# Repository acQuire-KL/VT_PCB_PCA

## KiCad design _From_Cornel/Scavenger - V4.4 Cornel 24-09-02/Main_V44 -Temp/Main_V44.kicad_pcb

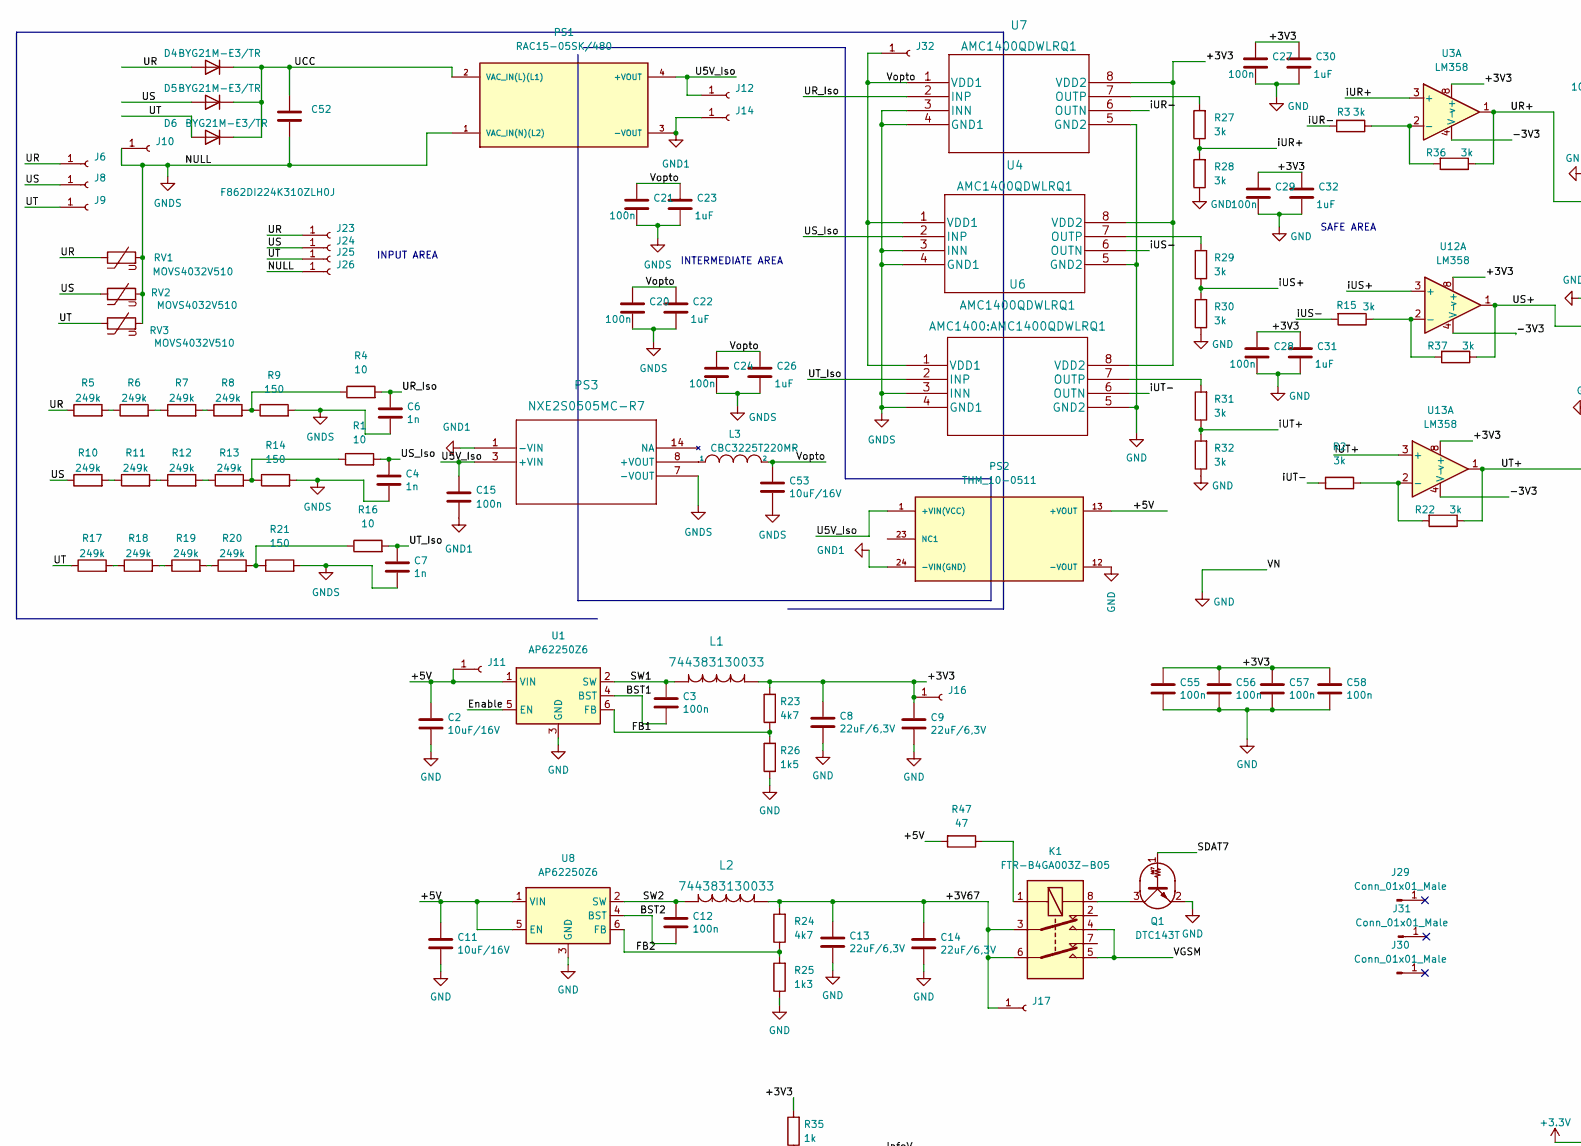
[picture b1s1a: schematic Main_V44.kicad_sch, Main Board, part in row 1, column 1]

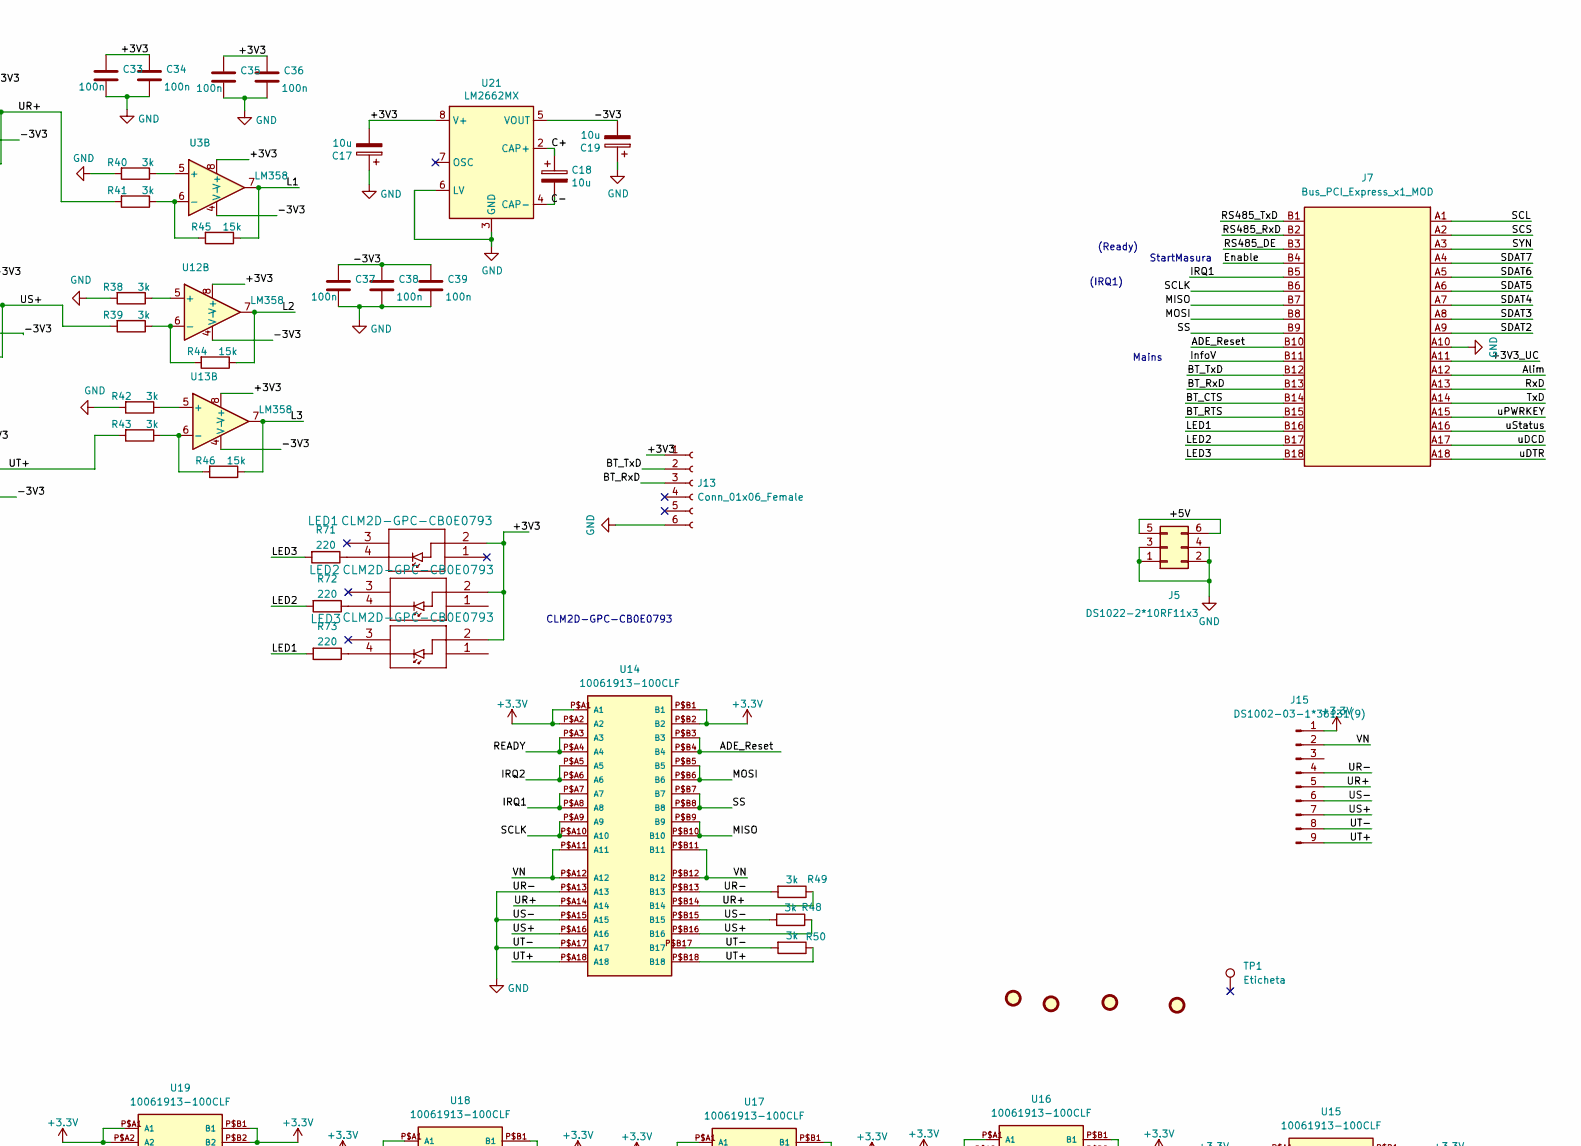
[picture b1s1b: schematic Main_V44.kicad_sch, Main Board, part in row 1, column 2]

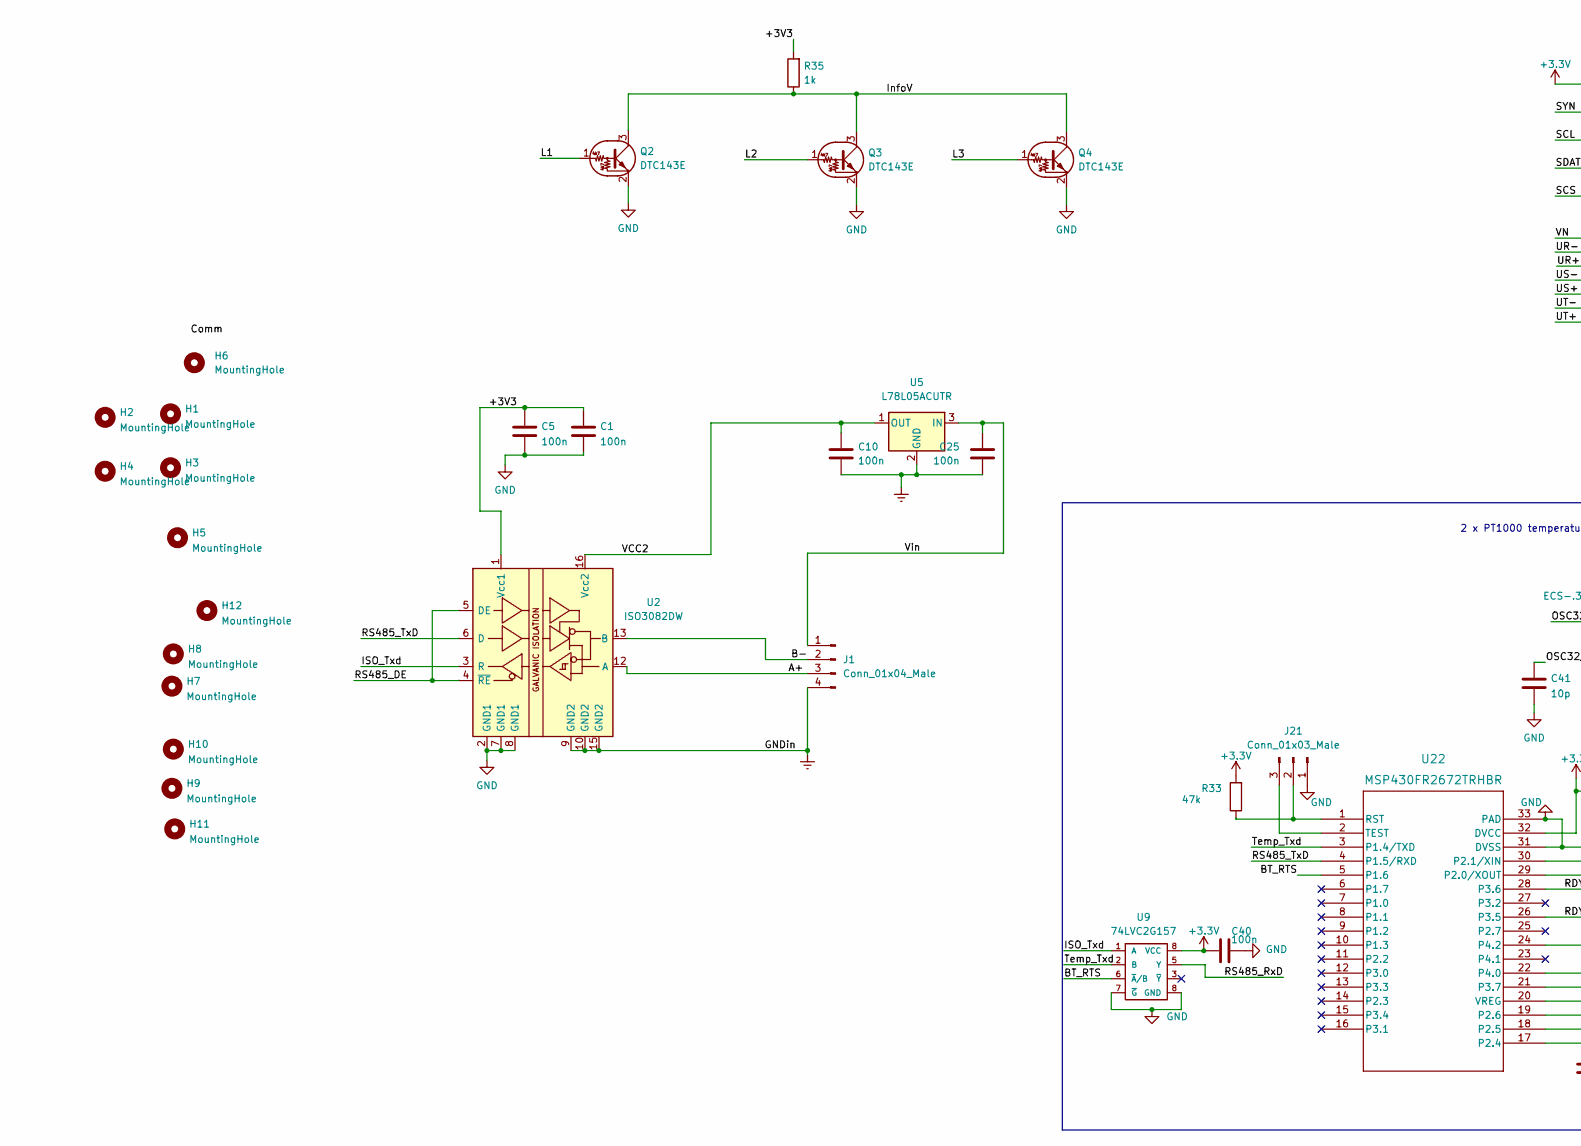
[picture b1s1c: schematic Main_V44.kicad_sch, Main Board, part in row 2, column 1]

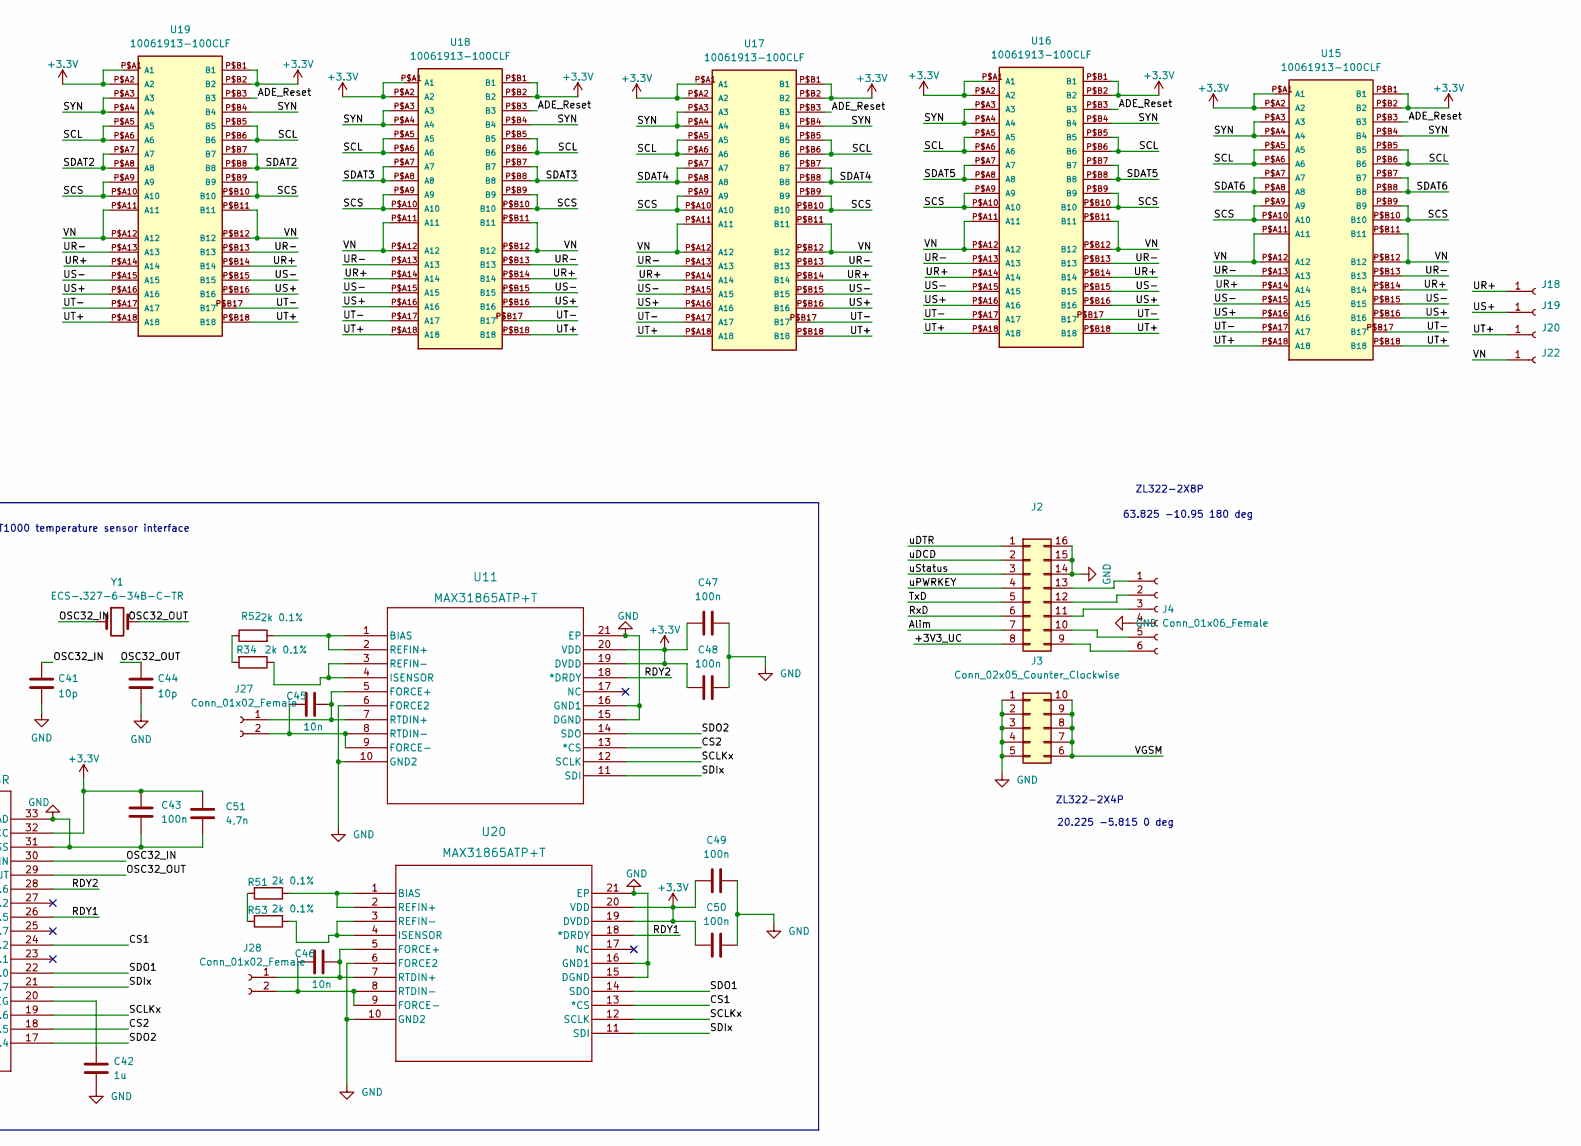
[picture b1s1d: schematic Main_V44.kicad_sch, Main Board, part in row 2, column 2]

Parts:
C1, C3, C5, C10, C12, C15, C20, C21, C24, C25, C27, C28, C29, C33, C34, C35, C36, C37, C38, C39, C40, C43, C47, C48, C49, C50, C55, C56, C57, C58: 100n; C_0603_1608Metric
C2, C11, C53: 10uF/16V; C_1206_3216Metric
C4, C6, C7: 1n; C_0603_1608Metric
C8, C9, C13, C14: 22uF/6,3V; C_1206_3216Metric
C17, C18, C19: 10u; C_1206_3216Metric
C22, C23, C26, C30, C31, C32: 1uF; C_0603_1608Metric
C41, C44: 10p; C_0603_1608Metric
C42: 1u; C_0603_1608Metric
C45, C46: 10n; C_0603_1608Metric
C51: 4,7n; C_0603_1608Metric
C52: F862DI224K310ZLH0J; C_Rect_L24.0mm_W7.0mm_P22.50mm_MKT
D4, D5, D6: BYG21M-E3/TR; D_SMA
FID1, FID2, FID3, FID4: Fiducial; Fiducial_1mm_Mask2mm
H1, H6: MountingHole; MountingHole_3.2mm_M3_ISO14580_Pad_TopBottom
H2, H3, H4, H5, H7, H8, H9, H10, H11, H12: MountingHole; MountingHole_3.2mm_M3
J1: Conn_01x04_Male; A2501-SR04-XH4AWB
J2: Conn_02x08_Counter_Clockwise; PinSocket_2x08_P2.54mm_Vertical_SMD_MOD
J3: Conn_02x05_Counter_Clockwise; PinSocket_2x05_P2.54mm_Vertical_SMD
J4, J13: Conn_01x06_Female; PinSocket_1x06_P2.54mm_Vertical
J5: DS1022-2*10RF11x3; PinHeader_2x03_P2.54mm_Horizontal
J6, J8, J9, J10, J11, J12, J14, J16, J17, J18, J19, J20, J22, J32: Conn_01x01_Female; TestPoint_DELTA
J7: Bus_PCI_Express_x1_MOD; BUS_PCIexpress_x1
J15: DS1002-03-1*36131(9); PinSocket_1x09_P2.54mm_Vertical
J21: Conn_01x03_Male; PinHeader_1x03_P2.54mm_Vertical
J23: Conn_01x01_Female; DELTA_SolderWire-1.5sqmm_1x01_D1.7mm_OD3.9mm
J24, J25, J26: Conn_01x01_Female; DELTA_R_SolderWire-1.5sqmm_1x01_D1.7mm_OD3.9mm
J27, J28: Conn_01x02_Female; TerminalBlock_bornier-2_P5.08mm
J29, J30, J31: Conn_01x01_Male; TestPoint_Pad_5.1x5.1mm
K1: FTR-B4GA003Z-B05; Relay_Fujitsu_FTR-B4GA003
L1, L2: 744383130033
L3: CBC3225T220MR; L_1206_3216Metric
LED1, LED2, LED3: CLM2D-GPC-CB0E0793
PS1: RAC15-05SK/480; CONV_RAC15-12SK_480; PARTREV 0/2022
PS2: THM_10-0511; CONV_THM_10-0511; PARTREV Jan 06, 2021
PS3: NXE2S0505MC-R7; NXE2_SINGLE_SURFACE_MUR
Q1: DTC143T; SOT-23
Q2, Q3, Q4: DTC143E; SOT-23
R1, R4, R16: 10; R_0603_1608Metric
R2, R3, R15, R22, R27, R28, R29, R30, R31, R32, R36, R37, R38, R39, R40, R41, R42, R43, R48, R49, R50: 3k; R_0603_1608Metric
R5, R6, R7, R8, R10, R11, R12, R13, R17, R18, R19, R20: 249k; R_2512_6332Metric
R9, R14, R21: 150; R_0603_1608Metric
R23, R24: 4k7; R_0603_1608Metric
R25: 1k3; R_0603_1608Metric
R26: 1k5; R_0603_1608Metric
R33: 47k; R_0603_1608Metric
R34, R51, R52, R53: 2k 0.1%; R_0603_1608Metric
R35: 1k; R_0603_1608Metric
R44, R45, R46: 15k; R_0603_1608Metric
R47: 47; R_0603_1608Metric
R71, R72, R73: 220; R_0603_1608Metric
RV1, RV2, RV3: MOVS4032V510; MOVS4032V460
TP1: Eticheta
U1, U8: AP62250Z6; SOT-563
U2: ISO3082DW; SOIC-16W_7.5x10.3mm_P1.27mm
U3, U12, U13: LM358; SO-8_3.9x4.9mm_P1.27mm
U4, U6, U7: AMC1400QDWLRQ1
U5: L78L05ACUTR; SOT-89-3
U9: 74LVC2G157; VSSOP-8_2.4x2.1mm_P0.5mm
U11, U20: MAX31865ATP+T; 21-0140L_T2055-5_MXM
U14, U15, U16, U17, U18, U19: 10061913-100CLF; MPN 10061913-100CLF
U21: LM2662MX; SO-8_3.9x4.9mm_P1.27mm
U22: MSP430FR2672TRHBR; VQFN32_5X5_TEX
Y1: ECS-.327-6-34B-C-TR; Crystal_SMD_EuroQuartz_EQ161-2Pin_3.2x1.5mm

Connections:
/+3V3_UC: J2.8, J7.A11
/+3V67: C13.1, C14.1, J17.1, K1.3, K1.6, L2.1, R24.2
/+5V: C2.1, C11.1, J5.5, J5.6, J11.1, PS2.13 (+VOUT), R47.2, U1.1 (VIN), U8.1 (VIN), U8.5 (EN)
/-3V3: C19.2, C37.1, C38.1, C39.1, U3.4 (V-), U12.4 (V-), U13.4 (V-), U21.5 (VOUT)
/A+: J1.3, U2.12 (A)
/ADE_Reset: J7.B10, U14.P$B3 (B3), U14.P$B4 (B4), U15.P$B3 (B3), U16.P$B3 (B3), U17.P$B3 (B3), U18.P$B3 (B3), U19.P$B3 (B3)
/Alim: J2.7, J7.A12
/B-: J1.2, U2.13 (B)
/BST1: C3.2, U1.4 (BST)
/BST2: C12.2, U8.4 (BST)
/BT_CTS: J7.B14
/BT_RTS: J7.B15, U9.6 (~A/B), U22.5 (P1.6)
/BT_RxD: J7.B13, J13.3
/BT_TxD: J7.B12, J13.2
/C+: C18.1, U21.2 (CAP+)
/C-: C18.2, U21.4 (CAP-)
/CS1: U20.13 (*CS), U22.24 (P4.2)
/CS2: U11.13 (*CS), U22.18 (P2.5)
/Enable: J7.B4, U1.5 (EN)
/FB1: R23.1, R26.2, U1.6 (FB)
/FB2: R24.1, R25.2, U8.6 (FB)
/IRQ1: J7.B5, U14.P$A7 (A7), U14.P$A8 (A8)
/IRQ2: U14.P$A5 (A5), U14.P$A6 (A6)
/ISO_Txd: U2.3 (R), U9.1 (A)
/InfoV: J7.B11, Q2.3 (C), Q3.3 (C), Q4.3 (C), R35.1
/L1: Q2.1 (B), R45.1, U3.7
/L2: Q3.1 (B), R44.1, U12.7
/L3: Q4.1 (B), R46.1, U13.7
/LED1: J7.B16, R73.2
/LED2: J7.B17, R72.2
/LED3: J7.B18, R71.2
/MISO: J7.B7, U14.P$B9 (B9), U14.P$B10 (B10)
/MOSI: J7.B8, U14.P$B5 (B5), U14.P$B6 (B6)
/OSC32_IN: C41.1, U22.30 (P2.1/XIN), Y1.1
/OSC32_OUT: C44.1, U22.29 (P2.0/XOUT), Y1.2
/RDY1: U20.18 (*DRDY), U22.26 (P3.5)
/RDY2: U11.18 (*DRDY), U22.28 (P3.6)
/READY: U14.P$A3 (A3), U14.P$A4 (A4)
/RS485_DE: J7.B3, U2.4 (~RE), U2.5 (DE)
/RS485_RxD: J7.B2, U9.5 (Y)
/RS485_TxD: J7.B1, U2.6 (D), U22.4 (P1.5/RXD)
/RxD: J2.6, J7.A13
/SCL: J7.A1, U15.P$A5 (A5), U15.P$A6 (A6), U15.P$B5 (B5), U15.P$B6 (B6), U16.P$A5 (A5), U16.P$A6 (A6), U16.P$B5 (B5), U16.P$B6 (B6), U17.P$A5 (A5), U17.P$A6 (A6), U17.P$B5 (B5), U17.P$B6 (B6), U18.P$A5 (A5), U18.P$A6 (A6), U18.P$B5 (B5), U18.P$B6 (B6), U19.P$A5 (A5), U19.P$A6 (A6), U19.P$B5 (B5), U19.P$B6 (B6)
/SCLK: J7.B6, U14.P$A9 (A9), U14.P$A10 (A10)
/SCLKx: U11.12 (SCLK), U20.12 (SCLK), U22.19 (P2.6)
/SCS: J7.A2, U15.P$A9 (A9), U15.P$A10 (A10), U15.P$B9 (B9), U15.P$B10 (B10), U16.P$A9 (A9), U16.P$A10 (A10), U16.P$B9 (B9), U16.P$B10 (B10), U17.P$A9 (A9), U17.P$A10 (A10), U17.P$B9 (B9), U17.P$B10 (B10), U18.P$A9 (A9), U18.P$A10 (A10), U18.P$B9 (B9), U18.P$B10 (B10), U19.P$A9 (A9), U19.P$A10 (A10), U19.P$B9 (B9), U19.P$B10 (B10)
/SDAT2: J7.A9, U19.P$A7 (A7), U19.P$A8 (A8), U19.P$B7 (B7), U19.P$B8 (B8)
/SDAT3: J7.A8, U18.P$A7 (A7), U18.P$A8 (A8), U18.P$B7 (B7), U18.P$B8 (B8)
/SDAT4: J7.A7, U17.P$A7 (A7), U17.P$A8 (A8), U17.P$B7 (B7), U17.P$B8 (B8)
/SDAT5: J7.A6, U16.P$A7 (A7), U16.P$A8 (A8), U16.P$B7 (B7), U16.P$B8 (B8)
/SDAT6: J7.A5, U15.P$A7 (A7), U15.P$A8 (A8), U15.P$B7 (B7), U15.P$B8 (B8)
/SDAT7: J7.A4, Q1.1 (B)
/SDIx: U11.11 (SDI), U20.11 (SDI), U22.21 (P3.7)
/SDO1: U20.14 (SDO), U22.22 (P4.0)
/SDO2: U11.14 (SDO), U22.17 (P2.4)
/SS: J7.B9, U14.P$B7 (B7), U14.P$B8 (B8)
/SW1: C3.1, L1.2, U1.2 (SW)
/SW2: C12.1, L2.2, U8.2 (SW)
/SYN: J7.A3, U15.P$A3 (A3), U15.P$A4 (A4), U15.P$B4 (B4), U16.P$A3 (A3), U16.P$A4 (A4), U16.P$B4 (B4), U17.P$A3 (A3), U17.P$A4 (A4), U17.P$B4 (B4), U18.P$A3 (A3), U18.P$A4 (A4), U18.P$B4 (B4), U19.P$A3 (A3), U19.P$A4 (A4), U19.P$B4 (B4)
/Temp_Txd: U9.2 (B), U22.3 (P1.4/TXD)
/TxD: J2.5, J7.A14
/U5V_Iso: C15.1, J12.1, PS1.4 (+VOUT), PS2.1 (+VIN(VCC)), PS3.3 (+VIN)
/UCC: C52.1, D4.1 (K), D5.1 (K), D6.1 (K), PS1.2 (VAC_IN(L)(L1))
/UR: D4.2 (A), J6.1, J23.1, R5.1, RV1.1
/UR+: J15.5, J18.1, R36.1, R41.2, R49.1, U3.1, U14.P$A14 (A14), U14.P$B14 (B14), U15.P$A14 (A14), U15.P$B14 (B14), U16.P$A14 (A14), U16.P$B14 (B14), U17.P$A14 (A14), U17.P$B14 (B14), U18.P$A14 (A14), U18.P$B14 (B14), U19.P$A14 (A14), U19.P$B14 (B14)
/UR_Iso: C6.1, R4.2, U7.2 (INP)
/US: D5.2 (A), J8.1, J24.1, R10.1, RV2.1
/US+: J15.7, J19.1, R37.1, R39.2, R48.1, U12.1, U14.P$A16 (A16), U14.P$B16 (B16), U15.P$A16 (A16), U15.P$B16 (B16), U16.P$A16 (A16), U16.P$B16 (B16), U17.P$A16 (A16), U17.P$B16 (B16), U18.P$A16 (A16), U18.P$B16 (B16), U19.P$A16 (A16), U19.P$B16 (B16)
/US_Iso: C4.1, R1.2, U4.2 (INP)
/UT: D6.2 (A), J9.1, J25.1, R17.1, RV3.1
/UT+: J15.9, J20.1, R22.1, R43.2, R50.1, U13.1, U14.P$A18 (A18), U14.P$B18 (B18), U15.P$A18 (A18), U15.P$B18 (B18), U16.P$A18 (A18), U16.P$B18 (B18), U17.P$A18 (A18), U17.P$B18 (B18), U18.P$A18 (A18), U18.P$B18 (B18), U19.P$A18 (A18), U19.P$B18 (B18)
/UT_Iso: C7.1, R16.2, U6.2 (INP)
/VCC2: C10.1, U2.16 (Vcc2), U5.1 (OUT)
/VGSM: J3.6, J3.7, J3.8, J3.9, J3.10, K1.4, K1.5
/Vin: C25.1, J1.1, U5.3 (IN)
/Vopto: C20.1, C21.1, C22.1, C23.1, C24.1, C26.1, C53.1, J32.1, L3.2, U4.1 (VDD1), U6.1 (VDD1), U7.1 (VDD1)
/iUR+: R27.1, R28.2, U3.3 (+)
/iUR-: R3.2, U7.6 (OUTN)
/iUS+: R29.1, R30.2, U12.3 (+)
/iUS-: R15.2, U4.6 (OUTN)
/iUT+: R31.1, R32.2, U13.3 (+)
/iUT-: R2.2, U6.6 (OUTN)
/uDCD: J2.2, J7.A17
/uDTR: J2.1, J7.A18
/uPWRKEY: J2.4, J7.A15
/uStatus: J2.3, J7.A16
Earth: C10.2, C25.2, J1.4, U2.9 (GND2), U2.10 (GND2), U2.15 (GND2), U5.2 (GND)
GND1: C15.2, J14.1, PS1.3 (-VOUT), PS2.24 (-VIN(GND)), PS3.1 (-VIN)
GNDS: C4.2, C6.2, C7.2, C20.2, C21.2, C22.2, C23.2, C24.2, C26.2, C52.2, C53.2, J10.1, J26.1, PS1.1 (VAC_IN(N)(L2)), PS3.7 (-VOUT), R9.2, R14.2, R21.2, RV1.2, RV2.2, RV3.2, U4.3 (INN), U4.4 (GND1), U6.3 (INN), U6.4 (GND1), U7.3 (INN), U7.4 (GND1)
unnamed: C42.2, U22.20 (VREG)
unnamed: C45.1, J27.2, U11.8 (RTDIN-), U11.9 (FORCE-)
unnamed: C45.2, J27.1, U11.5 (FORCE+), U11.7 (RTDIN+)
unnamed: C46.1, J28.2, U20.8 (RTDIN-), U20.9 (FORCE-)
unnamed: C46.2, J28.1, U20.5 (FORCE+), U20.7 (RTDIN+)
unnamed: J2.9, J4.6
unnamed: J2.10, J4.5
unnamed: J2.11, J4.3
unnamed: J2.12, J4.2
unnamed: J2.13, J4.1
unnamed: J21.2, R33.1, U22.1 (RST)
unnamed: J21.3, U22.2 (TEST)
unnamed: K1.1, R47.1
unnamed: K1.8, Q1.3 (C)
unnamed: L3.1, PS3.8 (+VOUT)
unnamed: LED1.4, R71.1
unnamed: LED2.4, R72.1
unnamed: LED3.4, R73.1
unnamed: R1.1, R13.2, R14.1
unnamed: R2.1, R22.2, U13.2 (-)
unnamed: R3.1, R36.2, U3.2 (-)
unnamed: R4.1, R8.2, R9.1
unnamed: R5.2, R6.1
unnamed: R6.2, R7.1
unnamed: R7.2, R8.1
unnamed: R10.2, R11.1
unnamed: R11.2, R12.1
unnamed: R12.2, R13.1
unnamed: R15.1, R37.2, U12.2 (-)
unnamed: R16.1, R20.2, R21.1
unnamed: R17.2, R18.1
unnamed: R18.2, R19.1
unnamed: R19.2, R20.1
unnamed: R27.2, U7.7 (OUTP)
unnamed: R29.2, U4.7 (OUTP)
unnamed: R31.2, U6.7 (OUTP)
unnamed: R34.1, U11.3 (REFIN-), U11.4 (ISENSOR)
unnamed: R34.2, R52.1
unnamed: R38.1, U12.5 (+)
unnamed: R39.1, R44.2, U12.6 (-)
unnamed: R40.1, U3.5 (+)
unnamed: R41.1, R45.2, U3.6 (-)
unnamed: R42.1, U13.5 (+)
unnamed: R43.1, R46.2, U13.6 (-)
unnamed: R51.1, U20.1 (BIAS), U20.2 (REFIN+)
unnamed: R51.2, R53.2
unnamed: R52.2, U11.1 (BIAS), U11.2 (REFIN+)
unnamed: R53.1, U20.3 (REFIN-), U20.4 (ISENSOR)

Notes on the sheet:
ZL322-2X4P
ZL322-2X8P
20.225 -5.815 0 deg
(Ready)
2 x PT1000 temperature sensor interface
Mains
(IRQ1)
CLM2D-GPC-CB0E0793
StartMasura
63.825 -10.95 180 deg
SAFE AREA
INPUT AREA
INTERMEDIATE AREA

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
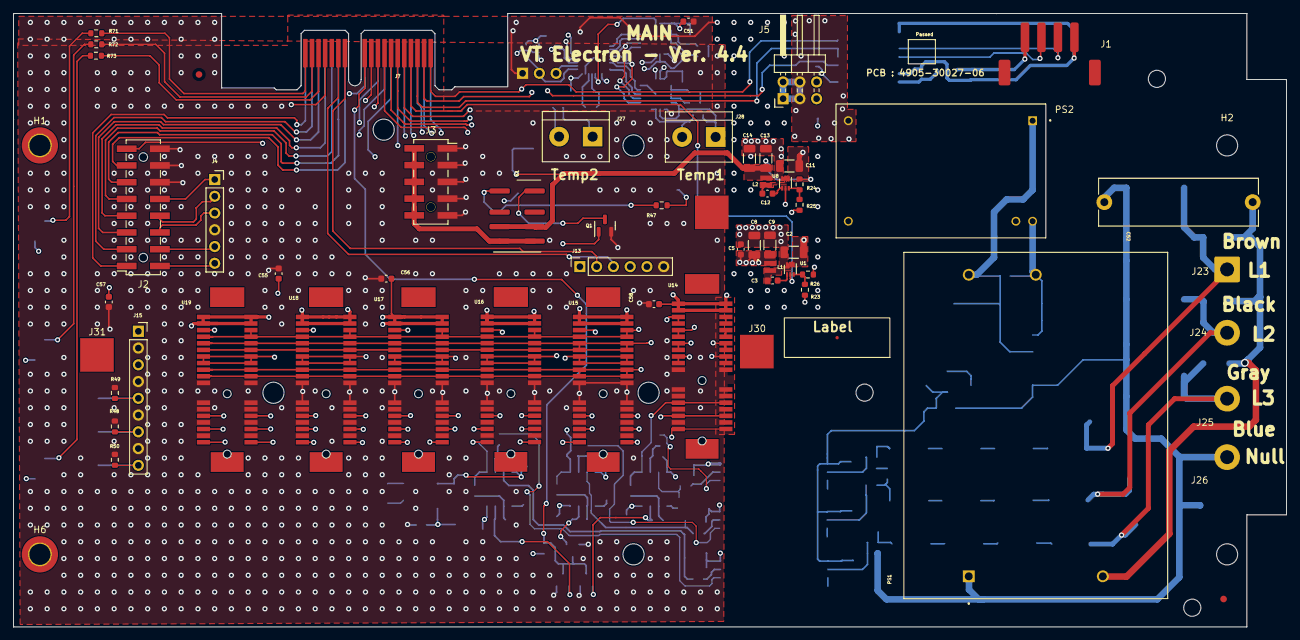
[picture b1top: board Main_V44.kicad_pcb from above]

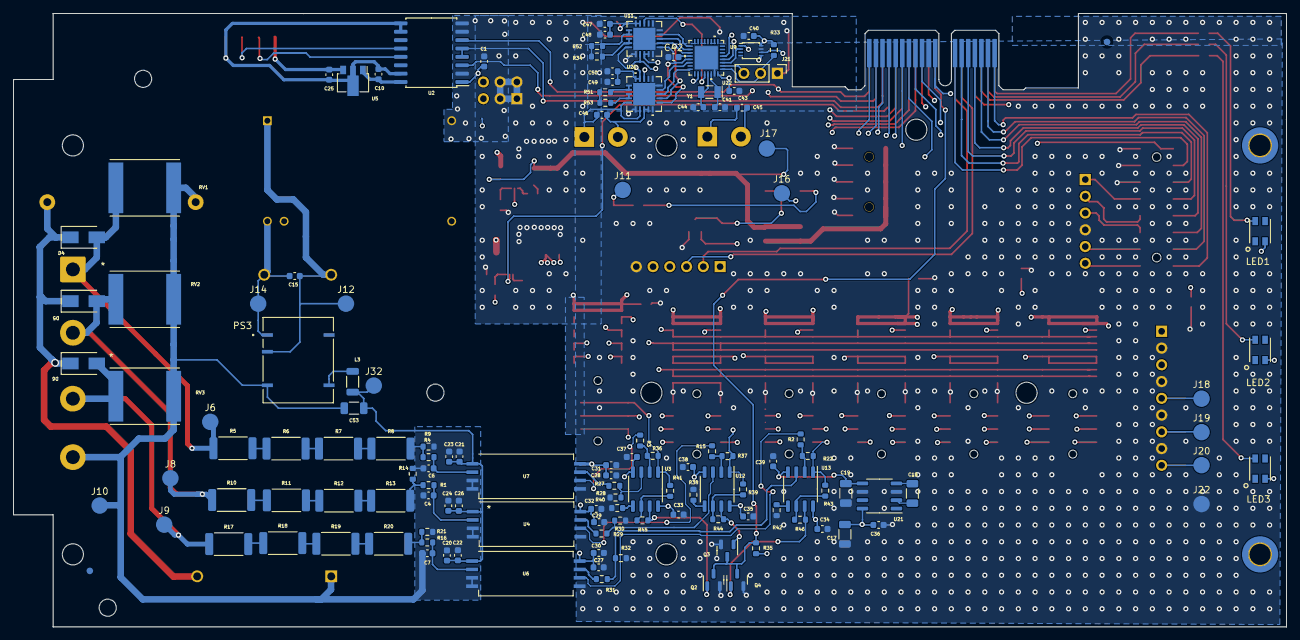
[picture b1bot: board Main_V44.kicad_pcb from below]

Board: 4 copper layers, 193.0 x 93.0 mm, 203 parts (131 on the bottom side), 138 nets.

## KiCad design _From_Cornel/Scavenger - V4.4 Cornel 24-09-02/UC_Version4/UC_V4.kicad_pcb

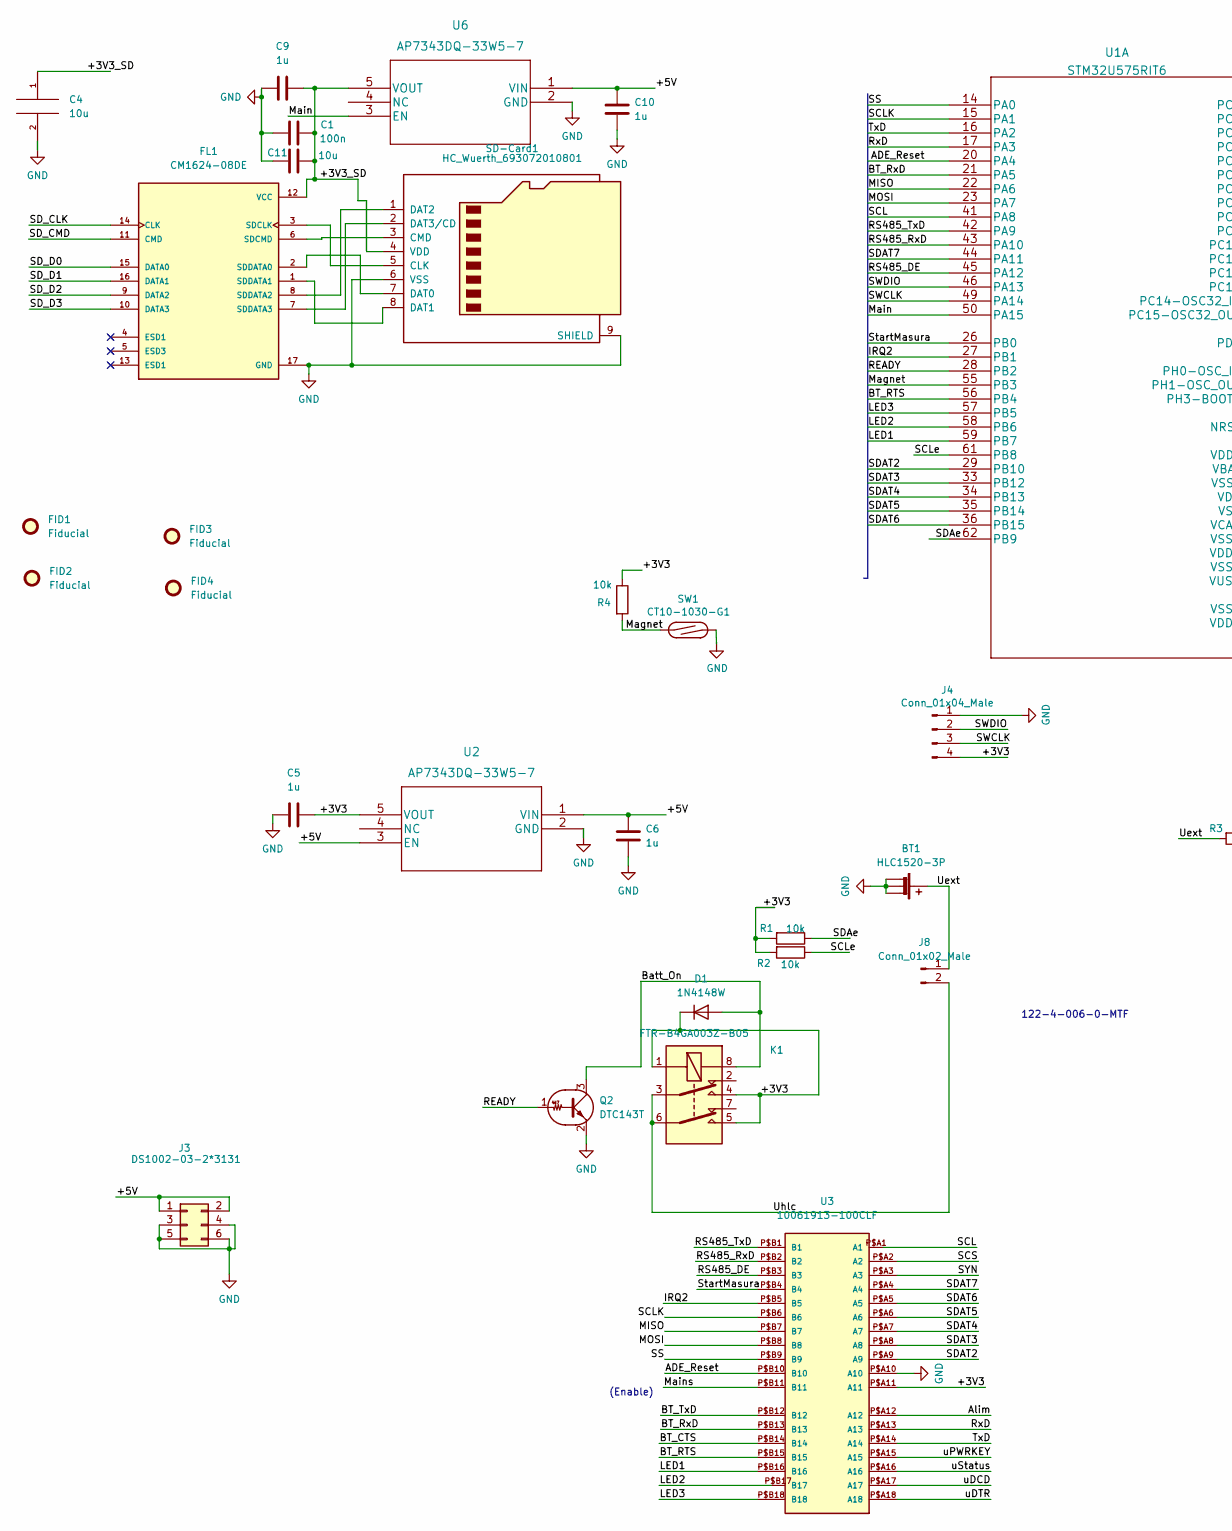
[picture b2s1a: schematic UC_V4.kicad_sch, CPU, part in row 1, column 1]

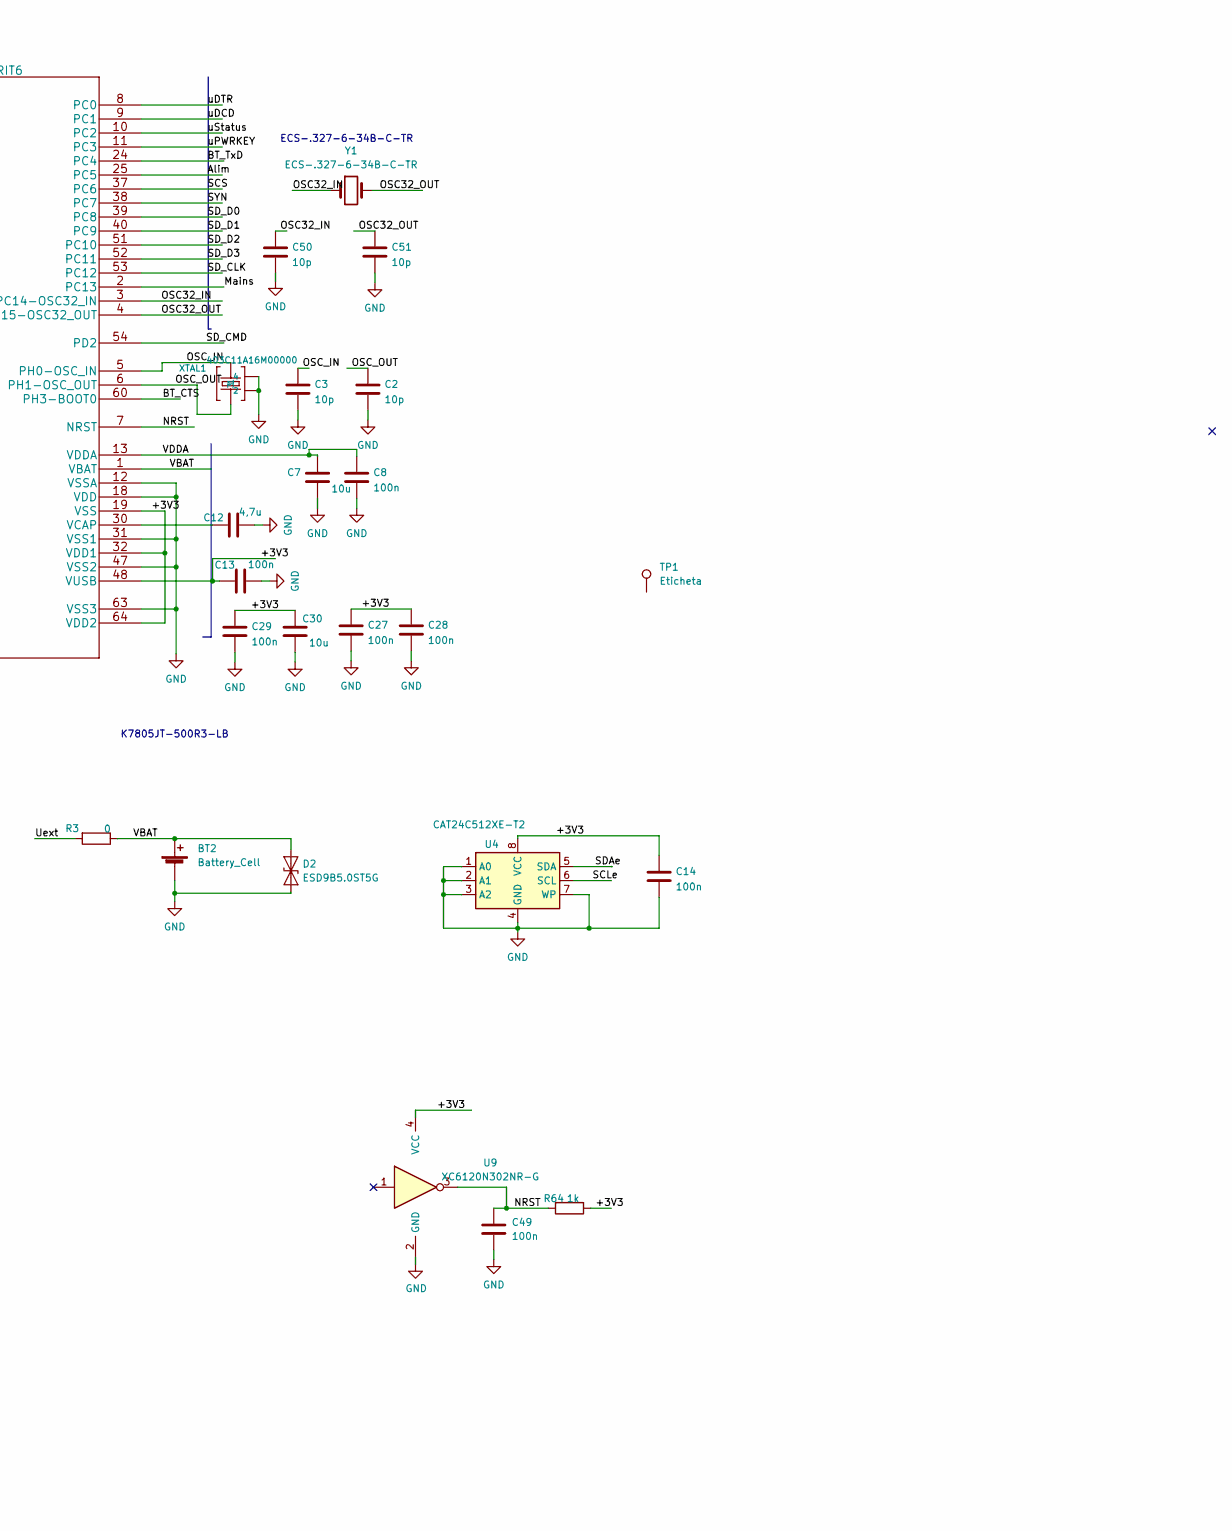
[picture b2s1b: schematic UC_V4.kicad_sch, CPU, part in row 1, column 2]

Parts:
BT1: HLC1520-3P
BT2: Battery_Cell; BatteryHolder_Keystone_3002_1x2032
C1, C8, C13, C14, C27, C28, C29, C49: 100n; C_0603_1608Metric
C2, C3, C50, C51: 10p; C_0603_1608Metric
C4, C7, C11, C30: 10u; C_1206_3216Metric
C5, C6, C9, C10: 1u; C_0603_1608Metric
C12: 4,7u; C_1206_3216Metric
D1: 1N4148W; D_SOD-123
D2: ESD9B5.0ST5G; SOD-923_ONS
FID1, FID2, FID3, FID4: Fiducial; Fiducial_1mm_Mask2mm
FL1: CM1624-08DE; FIL_CM1624; PARTREV 4
J3: DS1002-03-2*3131; PinSocket_2x03_P2.54mm_Vertical
J4: Conn_01x04_Male; PinHeader_1x04_P2.54mm_Vertical
J8: Conn_01x02_Male; PinHeader_1x02_P2.54mm_Vertical
K1: FTR-B4GA003Z-B05; Relay_Fujitsu_FTR-B4GA003
Q2: DTC143T; SOT-23
R1, R2, R4: 10k; R_0603_1608Metric
R3: 0; R_0603_1608Metric
R64: 1k; R_0603_1608Metric
SD-Card1: HC_Wuerth_693072010801; microSD_HC_Wuerth_693072010801
SW1: CT10-1030-G1; SW_SPST_REED_CT10-XXXX-G1
TP1: Eticheta
U1: STM32U575RIT6; LQFP-64_10x10mm_P0.5mm
U2, U6: AP7343DQ-33W5-7; AP3012KTR-G1
U3: 10061913-100CLF; MPN 10061913-100CLF
U4: CAT24C512XE-T2; SO-8_3.9x4.9mm_P1.27mm
U9: XC6120N302NR-G; SC-82AA
XTAL1: 403C11A16M00000; Crystal_SMD_SeikoEpson_TSX3225-4Pin_3.2x2.5mm
Y1: ECS-.327-6-34B-C-TR; Crystal_SMD_EuroQuartz_EQ161-2Pin_3.2x1.5mm

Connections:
/+3V3: C5.2, C13.1, C14.1, C27.1, C28.1, C29.1, C30.1, D1.1 (K), J4.4, K1.1, K1.4, K1.5, R1.2, R2.2, R4.1, R64.1, U1.19 (VSS), U1.32 (VDD1), U1.48 (VUSB), U1.64 (VDD2), U2.5 (VOUT), U3.P$A11 (A11), U4.8 (VCC), U9.4 (VCC)
/+3V3_SD: C1.2, C4.1, C9.2, C11.2, FL1.12 (VCC), SD-Card1.4 (VDD), U6.5 (VOUT)
/+5V: C6.1, C10.1, J3.1, J3.2, U2.1 (VIN), U2.3 (EN), U6.1 (VIN)
/ADE_Reset: U1.20 (PA4), U3.P$B10 (B10)
/Alim: U1.25 (PC5), U3.P$A12 (A12)
/BT_CTS: U1.60 (PH3-BOOT0), U3.P$B14 (B14)
/BT_RTS: U1.56 (PB4), U3.P$B15 (B15)
/BT_RxD: U1.21 (PA5), U3.P$B13 (B13)
/BT_TxD: U1.24 (PC4), U3.P$B12 (B12)
/Batt_On: D1.2 (A), K1.8, Q2.3 (C)
/IRQ2: U1.27 (PB1), U3.P$B5 (B5)
/LED1: U1.59 (PB7), U3.P$B16 (B16)
/LED2: U1.58 (PB6), U3.P$B17 (B17)
/LED3: U1.57 (PB5), U3.P$B18 (B18)
/MISO: U1.22 (PA6), U3.P$B7 (B7)
/MOSI: U1.23 (PA7), U3.P$B8 (B8)
/Magnet: R4.2, SW1.1, U1.55 (PB3)
/Main: U1.50 (PA15), U6.3 (EN)
/Mains: U1.2 (PC13), U3.P$B11 (B11)
/NRST: C49.1, R64.2, U1.7 (NRST), U9.3
/OSC32_IN: C50.1, U1.3 (PC14-OSC32_IN), Y1.1
/OSC32_OUT: C51.1, U1.4 (PC15-OSC32_OUT), Y1.2
/OSC_IN: C3.1, U1.5 (PH0-OSC_IN), XTAL1.3
/OSC_OUT: C2.1, U1.6 (PH1-OSC_OUT), XTAL1.1
/READY: Q2.1 (B), U1.28 (PB2)
/RS485_DE: U1.45 (PA12), U3.P$B3 (B3)
/RS485_RxD: U1.43 (PA10), U3.P$B2 (B2)
/RS485_TxD: U1.42 (PA9), U3.P$B1 (B1)
/RxD: U1.17 (PA3), U3.P$A13 (A13)
/SCL: U1.41 (PA8), U3.P$A1 (A1)
/SCLK: U1.15 (PA1), U3.P$B6 (B6)
/SCLe: R2.1, U1.61 (PB8), U4.6 (SCL)
/SCS: U1.37 (PC6), U3.P$A2 (A2)
/SDAT2: U1.29 (PB10), U3.P$A9 (A9)
/SDAT3: U1.33 (PB12), U3.P$A8 (A8)
/SDAT4: U1.34 (PB13), U3.P$A7 (A7)
/SDAT5: U1.35 (PB14), U3.P$A6 (A6)
/SDAT6: U1.36 (PB15), U3.P$A5 (A5)
/SDAT7: U1.44 (PA11), U3.P$A4 (A4)
/SDAe: R1.1, U1.62 (PB9), U4.5 (SDA)
/SD_CLK: FL1.14 (CLK), U1.53 (PC12)
/SD_CMD: FL1.11 (CMD), U1.54 (PD2)
/SD_D0: FL1.15 (DATA0), U1.39 (PC8)
/SD_D1: FL1.16 (DATA1), U1.40 (PC9)
/SD_D2: FL1.9 (DATA2), U1.51 (PC10)
/SD_D3: FL1.10 (DATA3), U1.52 (PC11)
/SS: U1.14 (PA0), U3.P$B9 (B9)
/SWCLK: J4.3, U1.49 (PA14)
/SWDIO: J4.2, U1.46 (PA13)
/SYN: U1.38 (PC7), U3.P$A3 (A3)
/StartMasura: U1.26 (PB0), U3.P$B4 (B4)
/TxD: U1.16 (PA2), U3.P$A14 (A14)
/Uext: BT1.1 (+), J8.1, R3.2
/Uhlc: J8.2, K1.3, K1.6
/VBAT: BT2.1 (+), D2.2 (A2), R3.1, U1.1 (VBAT)
/VDDA: C7.1, C8.1, U1.13 (VDDA)
/uDCD: U1.9 (PC1), U3.P$A17 (A17)
/uDTR: U1.8 (PC0), U3.P$A18 (A18)
/uPWRKEY: U1.11 (PC3), U3.P$A15 (A15)
/uStatus: U1.10 (PC2), U3.P$A16 (A16)
GND: BT1.2 (-), BT1.3 (-), BT1.4 (-), BT2.2 (-), C1.1, C2.2, C3.2, C4.2, C5.1, C6.2, C7.2, C8.2, C9.1, C10.2, C11.1, C12.2, C13.2, C14.2, C27.2, C28.2, C29.2, C30.2, C49.2, C50.2, C51.2, D2.1 (A1), FL1.17 (GND), J3.3, J3.4, J3.5, J3.6, J4.1, Q2.2 (E), SD-Card1.6 (VSS), SD-Card1.9 (SHIELD), SW1.2, U1.12 (VSSA), U1.18 (VDD), U1.31 (VSS1), U1.47 (VSS2), U1.63 (VSS3), U2.2 (GND), U3.P$A10 (A10), U4.1 (A0), U4.2 (A1), U4.3 (A2), U4.4 (GND), U4.7 (WP), U6.2 (GND), U9.2 (GND), XTAL1.2, XTAL1.4
unnamed: C12.1, U1.30 (VCAP)
unnamed: FL1.1 (SDDATA1), SD-Card1.8 (DAT1)
unnamed: FL1.2 (SDDATA0), SD-Card1.7 (DAT0)
unnamed: FL1.3 (SDCLK), SD-Card1.5 (CLK)
unnamed: FL1.6 (SDCMD), SD-Card1.3 (CMD)
unnamed: FL1.7 (SDDATA3), SD-Card1.2 (DAT3/CD)
unnamed: FL1.8 (SDDATA2), SD-Card1.1 (DAT2)

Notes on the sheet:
ECS-.327-6-34B-C-TR
K7805JT-500R3-LB
(Enable)
122-4-006-0-MTF

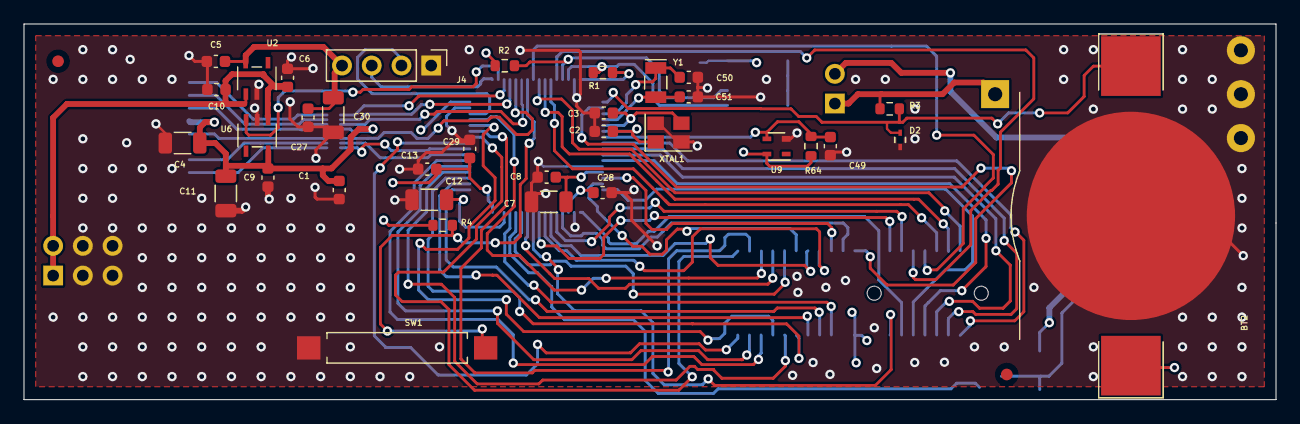
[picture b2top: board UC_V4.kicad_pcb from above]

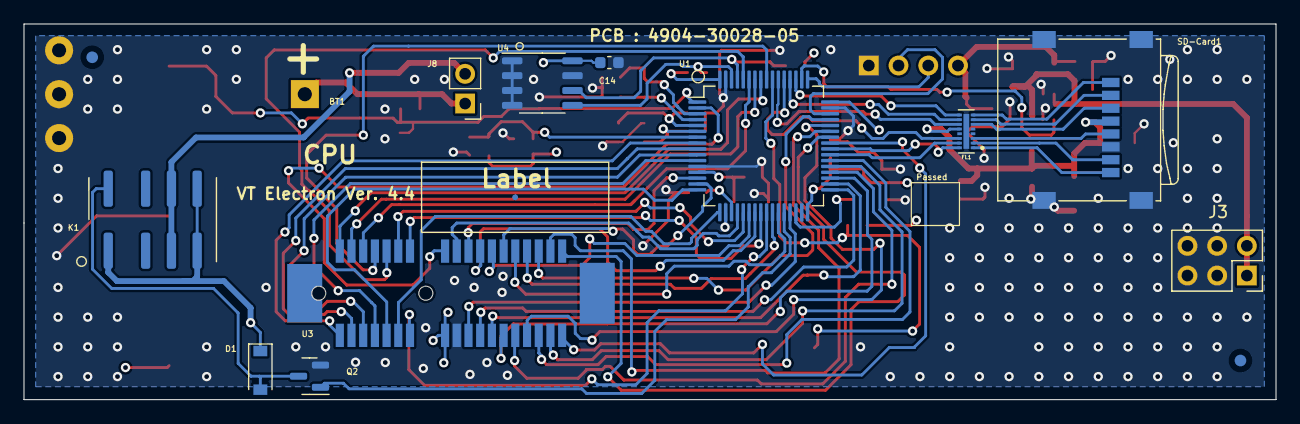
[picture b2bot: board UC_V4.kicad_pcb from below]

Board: 4 copper layers, 107.0 x 32.1 mm, 51 parts (13 on the bottom side), 68 nets.

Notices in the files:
parts and their libraries:
Copyright 2021 Accelerated Designs. All rights reserved.
